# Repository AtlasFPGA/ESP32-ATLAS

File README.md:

# ESP32-ATLAS
   Diseño en desarrollo para el ESP32 DEV KIT V1 usado de forma básica con sus  25 señales,se necesita disponer de un VGA64.
   No podíamos dejar pasar la oportunidad de alojar el ESP32 en el interior de la I/O BOARD ATLAS,este microcontroladro lleva muchos años en el mercado,tant es así que el ESP32 sigue siendo un producto puntero.
   Es importantísimo tener su Software en ATLAS, y con la tercera iteración de correspondencia de pines cubre toda la placa I/O BOARD ATLAS.
   La inicialización de FABGL con su configuración en la mayoría de las placas es la siguiente.
inicialización VGA FABGL:

   Vídeo que muestra, el correcto funcionamiento del recolocador que nos permitirá jugar con audio amplificado, i2s así como i2c en el futuro.

---

## Correcto funcionamiento recolocador ESP32:

---

VGAController.begin(GPIO_NUM_22, GPIO_NUM_21, GPIO_NUM_19, GPIO_NUM_18, GPIO_NUM_5, GPIO_NUM_4, GPIO_NUM_23, GPIO_NUM_15);

Leyendo el quema vemos que significado tiene de señales con sus nombres lógicos de los bits de color así como la frecuencia horizontal y vertical.

VGAController.begin(RED_1, RED_0 , GREEN_1, GREEN_0, BLUE_1, BLUE_0, H_SYNC, V_SYNC)

Inicialización ESP32 en ATLAS con el recolocador creado:

## VGAController.begin(GPIO_NUM_32, GPIO_NUM_33, GPIO_NUM_27, GPIO_NUM_4, GPIO_NUM_17, GPIO_NUM_13, GPIO_NUM_16, GPIO_NUM_15);

El recolocador de ATLAS tiene una colocación diferente.
---

Colocación del ESP32 en la placa I/O Board ATLAS Morada:

---

Placa "La Roja" vista con el recolocador ESP32 desde el bus del sbc:

---

Ensamblado ESP32 visto desde los puertos ps2 y db9 norma atari:

---

Visión de la placa recolocadora ESP32 superior:

---
Visión de la placa recolocadora ESP32 infernior:

---   

# Versión final sin amplificación de sonido:

---   

# Vídeo del proceso de desarrollo del recolocador para ESP32 DEV KIT V1; así como mostrar el funcionamiento del VGA64 222+HS+VS de la placa I/O Board ATLAS:

---

señales ATLAS| aclaración en ESP32 DEV KIT 1 | numero pines
| :--- | ---: | :---:
Señal VGA64 | Casi todos los cores de ESP32 usan 64colores esquema 222+HS+VS | 8
Señal JOYSTICK DB9 | En preparación ATARI-PADDLE-ATLAS  | 6
Señal SD SPI | las señales QPI se usan en modo SPI| 4
Señal PS2 TECLADO  | Protocolo PS/2 | 2
Señal PS2 RATÓN | Protocolo PS/2 | 2
Señal Sonido Estereo | sonido delta sigma_(12bits) o un pwm_(10bits), DAC_ESP32(8bits)| 2
Señal Transmisión y Recepcion | RX TX sin gestión de flujo| 2
Señal EAR | Señal de entrada | 1

   No hay lugar para Las Señales de RX y TX como GPIOS, se tendrá que acceder desde el USB.
   En este diseño son Necesarias 27 señales, pero el ESP32 DEV KIT V1 dispone de 25 patillas/señales de las cuales 4 son de entrada, ahí conectamos las direcciones del mando de juegos de norma ATARI en el bus DB9.

   Inicialmente antes de realizar el recolocador final,hemos usado el esquema de bitluni:
   
   http://www.fabglib.org/conf_v_g_a.html
   
   Con la siguiente disposición de pines para la primera iteración de pines:
   
   VGAController.begin(GPIO_NUM_22, GPIO_NUM_21, GPIO_NUM_19, GPIO_NUM_18, GPIO_NUM_5, GPIO_NUM_4, GPIO_NUM_23, GPIO_NUM_15);

##   Nota importante fijarse en los 4 pines que sólo permiten señales de entrada corresponden a los GPIO36, GPIO39, GPIO34, y GPIO35.

---

# ASIGNACIÓN ACTUAL; buscando tener el I2C con pull up en el DB9 y los 2 DAC de 8bits de resolución en la salida de sonido:
   los GPIO asociados a la salida de los dac de 8bit cada uno son, el GPIO25 y GPIO26.
   Esta es tercera iteración en su configuración final para el recolocador, a nivel lógico, sin amplificación de la señal de audio, para habilitar el puerto de audio con tensiones, es necesario cortar 2 pad stereo para que no llegue la señal a la I/O BOARD ATLAS, y estañar los pads que llevan las señales ESP_AUDIO_8BIT, al conector con tensión 3v3 y GND.

señales ATLAS | Patillaje izquierda | patilaje derecha | señales ATLAS
| ---: | ---: | ---: | :---: 
ENABLE| ENABLE | GPIO23| T14_SD_MOSI
J14_JOY_UP| GPIO36 | GPIO22| K15_JOY_FIRE1
R1_JOY_DOWN| GPIO39 | GPIO01 | MOUSE_DAT
N16_JOY_RIGHT| GPIO34 | GPIO03 | MOUSE_CLK
T15_JOY_LEFT| GPIO35 | GPIO21| K16_JOY_FIRE2
TMDS_2_P| GPIO32 | GPIO19 | R13_SD_MISO
TMDS_2_N| GPIO33 | GPIO18 | T13_SD_CLK
R11_RIGHT| GPIO25 | GPIO05 | R12_SD_CS
T12_LEFT| GPIO26 |GPIO17 | TMDS_O_P
TMDS_1_P| GPIO27 | GPIO16 | TMDSC_N
ATLAS Mini -> L2_KCLK,Morada -> K2_KDAT| GPIO14 | GPIO04 | TMDS_1_N
ATLAS Mini -> K2_KDAT,Morada -> L2_KCLK| GPIO12 | GPIO02 | EAR
TMDS_0_N| GPIO13 | GPIO15 | TMDSC_P
GND| GND | GND| GND
+5V| VIN | +3V3| +3V3

---
# TABLA EQUIVALENCIAS SALIDA CONECTOR DE VÍDEO DIGITAL
Nomenclatura DVI | Pares diferenciales | VGA64 | SCART128 | ZX-SCART
| ---: | ---: | ---: | ---: |:---: 
TMDS[0]|CLK- | HS | CSYNC | CSYNC
TMDS[1]|CLK+ | VS | G[0]  | BRIGHT
TMDS[2]|0-   | BLUE[0] | BLUE[0] | I2S_DIN_SD 
TMDS[3]|0+   | BLUE[1] | BLUE[1] | B
TMDS[4]|1-   | GREEN[0] | G[1] | I2S_BCLK_SCK
TMDS[5]|1+   | GREEN[1] | G[2] | G
TMDS[6]|2-   | RED[0] | RED[0] | I2S_LRC_WS
TMDS[7]|2+   | RED[1] | RED[1] | R

Las señales por determinar del módulo ZX-SCART llevan al menos en serie una resistencia de 270 ohm, pero al ser 3 señales se puede luchar icorporar al DAC de 15 colores un I2S, se han reflejado tanto la terminología de DAC como Micrófono por I2S.

Nota: en modo DVI y anulando los pares diferenciales negativos es decir a 0V, una señal de baja resolución tendría que generar los datos para los 3 colores en digital, y un reloj constate y 5 veces más veloz que el reloj de pixel asociado a su misma resolucion en analógico, en total 4 señales de vídeo digital, no sabemos si estas señales DVI pueden ser generadas.

---

   Esquema de referencia usado al inicio de las iteraciones:

---

   Lo que hace un total de 25 pines GPIO, para aumentar el diseño, esta el DB9 con 6 pines en PULL UP (Consultar esquema ATLAS-MINI), permite ampliarse el modelo existente mediante integrados I2C, con un buses de entrada salida en el bus DB9, tener en cuenta de las otras 4 señales, obligatoriamente tiene que ser señales de entrada.
   
   Consulta del esquema ATLAS MINI "La Roja" con licencia CERN OHL V2 STRICT:
   
   https://github.com/AtlasFPGA/BASECARRIERBOARDATLAS
   
   Consulta del esquema en easyeda:
   
   https://oshwlab.com/subcritical/carrier_io_board_atlas_mini_copy
   
## Dimensiones:

## Las características del Esp32:

Los lenguajes de programación más usados para NodeMCU ESP32, son Arduino y MicroPython. Ambos son de código abierto y cuentan con herramientas de desarrollo gratuitas.
 
## Especificaciones:

• Placa: ESP32 DEVKIT V1 (Espressif)

• SoM (System on module): ESP-WROOM-32 (Espressif)

• SoC (System on chip): ESP32 (ESP32-D0WDQ6)

• Procesador: Tensilica Xtensa Dual-Core 32-bit LX6.

• Frecuencia del reloj: 160 a 240 Mhz.

• Desempeño: Hasta 600 DMIPS

• Memoria:

448 KByte ROM

520 KByte SRAM

16 KByte SRAM in RTC (Real Time Clock)

QSPI Flash/SRAM, 4 MBytes

• Número total de pines GPIO: 25

• WiFi con antena integrada: estándar 802.11 b/g/n. Velocidad de 150.0 Mbps

• Bluetooth: BLE (Bluetooth Low Energy) y Bluetooth Classic

• Interfaz USB-Serial CP2102 on board.

• Modo de funcionamiento Low Power.

• Peripheral Input/Output (25 pines GPIO)

• ADCs (Convertidores Analógico Digital) de 12 bits

• DACs (Convertidores Digital Analógico) de 8 bits

• I²C (Inter-Integrated Circuit)

• UART (Universal Asynchronous Receiver/Transmitter)

• SPI (Serial Peripheral Interface)

• I²S (Integrated Interchip Sound)

• RMII (Reduced Media-Independent Interface)

• PWM (Pulse-Width Modulation).

• Regulador de 3.3 volts on board.

• Voltaje de Alimentación (conector MicroUSB): 5v, 0.5A

• Niveles de voltaje de entradas/salidas: 3.3v

• Corriente máxima en salidas: IOH=40ma (source), IOL=28ma (sink).

- Dimensiones: 51.5 mm x 28.3 mm x 12 mm

- Distancia entre pines: estándar 2.54 mm

- Distancia entre ambas filas de pines: 26.0 mm

- Número total de pines: 30

   Fuente de características y mapeado de pines del microcontrolador de Espressif ESP32.

https://www.puntoflotante.net/NODEMCU-ESP32-DEVKIT-V1-STARTER-KIT.htm

##   En total ATLAS pone a dispocisión con el recolocador ESP32-ATLAS unas 25 señales, completando todas las señales que le puede brindar la I/O BOARD ATLAS: 

Si   hubiera una linea a mayores disponible sería muy interesante que actuara automáticamente un CS_PADDLE sobre el ATARI-PADDLE-ATLAS.

---

---

---

---

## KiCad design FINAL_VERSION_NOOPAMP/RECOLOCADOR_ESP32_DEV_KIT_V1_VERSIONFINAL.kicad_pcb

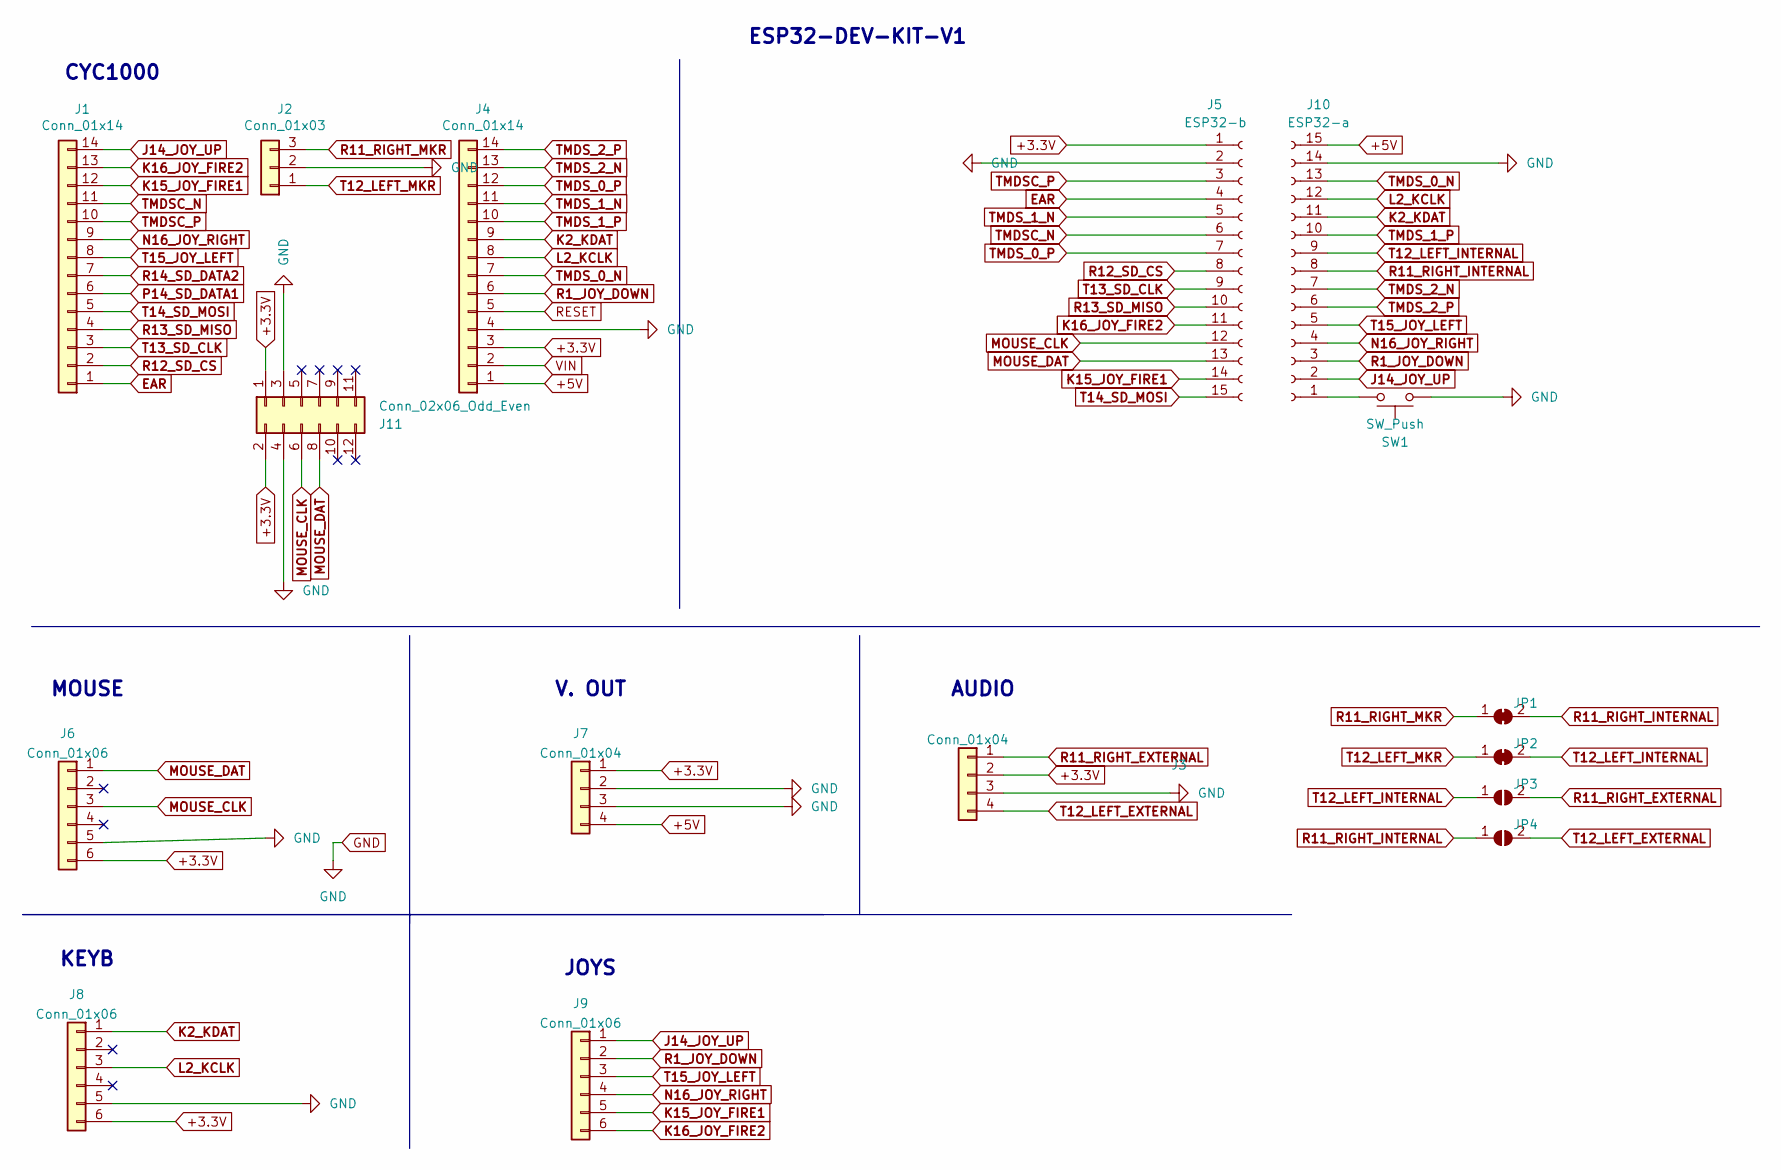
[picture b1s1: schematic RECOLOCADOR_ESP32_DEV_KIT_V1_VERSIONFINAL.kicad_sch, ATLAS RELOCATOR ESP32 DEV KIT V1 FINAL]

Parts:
J1, J4: Conn_01x14; PinHeader_1x14_P2.54mm_Vertical
J2: Conn_01x03; PinHeader_1x03_P2.54mm_Vertical
J3, J7: Conn_01x04; PinHeader_1x04_P2.54mm_Vertical
J5: ESP32-b; PinSocket_1x15_P2.54mm_Vertical
J6, J8, J9: Conn_01x06; PinHeader_1x06_P2.54mm_Vertical
J10: ESP32-a; PinSocket_1x15_P2.54mm_Vertical
J11: Conn_02x06_Odd_Even; PinHeader_2x06_P2.54mm_Vertical
JP1, JP2: SolderJumper_2_Bridged; SolderJumper-2_P1.3mm_Bridged2Bar_RoundedPad1.0x1.5mm
JP3, JP4: SolderJumper_2_Open; SolderJumper-2_P1.3mm_Open_RoundedPad1.0x1.5mm
SW1: SW_Push; SW_PUSH_6mm

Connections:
+3.3V: J3.2, J4.3, J5.1, J6.6, J7.1, J8.6, J11.1, J11.2
+5V: J4.1, J7.4, J10.15
EAR: J1.1, J5.4
GND: J2.2, J3.3, J4.4, J5.2, J6.5, J7.2, J7.3, J8.5, J10.14, J11.3, J11.4, SW1.2
J14_JOY_UP: J1.14, J9.1, J10.2
K2_KDAT: J4.9, J8.1, J10.11
K15_JOY_FIRE1: J1.12, J5.14, J9.5
K16_JOY_FIRE2: J1.13, J5.11, J9.6
L2_KCLK: J4.8, J8.3, J10.12
MOUSE_CLK: J5.12, J6.3, J11.6
MOUSE_DAT: J5.13, J6.1, J11.8
N16_JOY_RIGHT: J1.9, J9.4, J10.4
unnamed: J10.1, SW1.1
P14_SD_DATA1: J1.6
R1_JOY_DOWN: J4.6, J9.2, J10.3
R11_RIGHT_EXTERNAL: J3.1, JP3.2 (B)
R11_RIGHT_INTERNAL: J10.8, JP1.2 (B), JP4.1 (A)
R11_RIGHT_MKR: J2.3, JP1.1 (A)
R12_SD_CS: J1.2, J5.8
R13_SD_MISO: J1.4, J5.10
R14_SD_DATA2: J1.7
RESET: J4.5
T12_LEFT_EXTERNAL: J3.4, JP4.2 (B)
T12_LEFT_INTERNAL: J10.9, JP2.2 (B), JP3.1 (A)
T12_LEFT_MKR: J2.1, JP2.1 (A)
T13_SD_CLK: J1.3, J5.9
T14_SD_MOSI: J1.5, J5.15
T15_JOY_LEFT: J1.8, J9.3, J10.5
TMDSC_N: J1.11, J5.6
TMDSC_P: J1.10, J5.3
TMDS_0_N: J4.7, J10.13
TMDS_0_P: J4.12, J5.7
TMDS_1_N: J4.11, J5.5
TMDS_1_P: J4.10, J10.10
TMDS_2_N: J4.13, J10.7
TMDS_2_P: J4.14, J10.6
VIN: J4.2

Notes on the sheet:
MOUSE
CYC1000
AUDIO
KEYB
JOYS
ESP32-DEV-KIT-V1
V. OUT

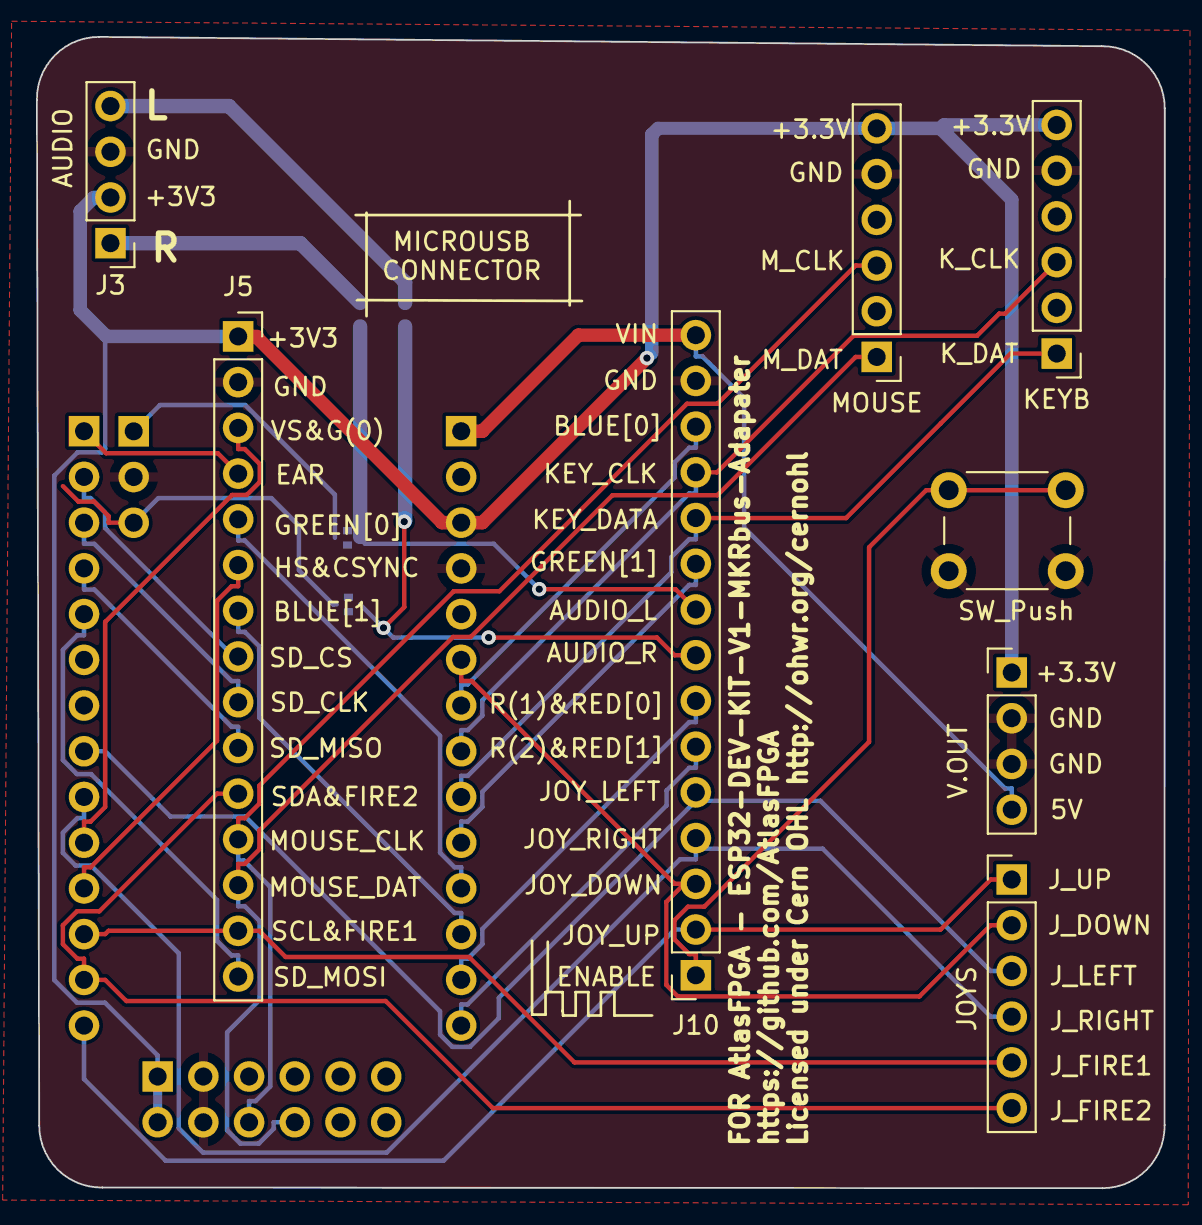
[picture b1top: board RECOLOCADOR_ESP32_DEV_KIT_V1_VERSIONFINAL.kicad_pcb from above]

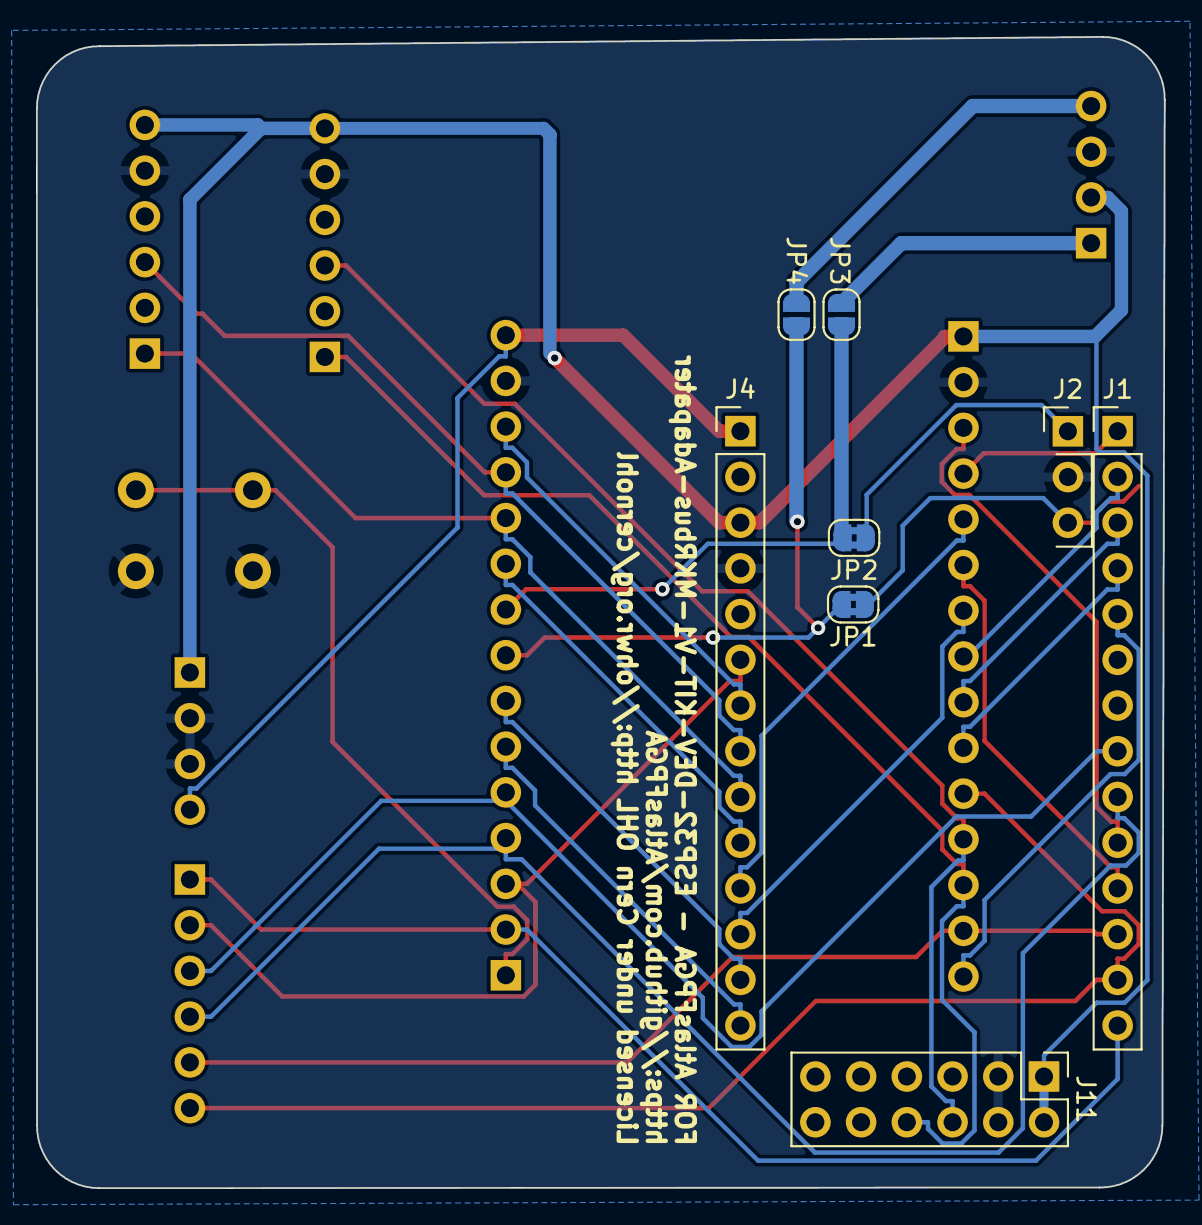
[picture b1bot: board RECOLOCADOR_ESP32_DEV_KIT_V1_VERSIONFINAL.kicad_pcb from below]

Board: 2 copper layers, 62.7 x 64.0 mm, 16 parts (8 on the bottom side), 33 nets.

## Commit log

2023-04-20 Subida de imágenes protipo ESP32-ATLAS.
    Esta vez como hay muchos modelos de ESP32, así como pineados para la VGA222, He optado por una forma clásica de afrontar el problema creando primero un modelo real.
    Se fija el modelo más económico de ESP32 y el más accesibles desde hace casi 8 años, el ESP32 DEV KIT V1.
2023-04-20 Crear un readme con las imágenes iniciales de ESP32-ATLAS
2023-04-20 Especificaciones ESP32
2023-04-20 Pineado ESP32
    Pineado para la versión ESP32 DEV KIT V1, la más usada de todas las versiones de ESP32.
2023-04-20 Añadido Los señales del microcontrolador ESP32 DEV KIT V1
2023-04-20 Agregar características ESP32 DEV KIT V1
2023-04-20 Mejoras en la información relativa al ESP32.
2023-04-20 Información del desarrollo del ESP32-ATLAS
2023-04-20 Añadidas las señales RX y TX sin control de flujo.
2023-04-20 Actualización información ESP32 DEV KIT V1
2023-04-20 Actualizar información ESP32 DEV KIT V1
2023-04-20 Actualización señales I/O BOARD ATLAS, en ESP32.
2023-04-20 Actualizaciones de información sobre el bus multipropósito DB9.
2023-04-20 Añadidas las direcciones de easyeda y kicad de I/O BOARD ATLAS MINI
2023-04-20 Actualización de direcciones easyeda I/O BOARD ATLAS MINI
2023-04-21 Actualización señales en el diseño del ESP32-ATLAS
2023-04-21 Añadidas correspondencias señales ESP32 con I/O Board ATLAS
2023-04-21 Subida paletas y pineado ESP32
2023-04-21 Añadir paletas de colores y pineado del ESP32 DEV KIT V1
2023-04-21 Tabla de correspondencias I/O Board ATLAS y ESP32
2023-04-21 Añadido esquemático de FabGL
2023-04-21 Actualizar correspondencias I/O BOARD ATLAS con ESP32
2023-06-02 Verificación funcionamiento con una placa de prototipo ESP32 en VGA64 con I/O BOARD ATLAS
2023-06-02 ESP32 DEV KIT V1 con la configuración FABGL en I/O BOARD ATLAS
2023-06-04 Nueva asignación final con todos los pines en uso, disponible spi, así como i2c en el puerto DB9.
2023-06-04 Aclaración del modelo kicad de ESP32 KIT V1, copando todos los puertos de la placa I/O Board ATLAS.
2023-06-04 Diseño de recolocador ESP32 DEV KIT V1, usando la misma terminología de recolocador de @Shaeon
2023-06-04 Diseño de recolocador ESP32 DEV KIT V1, usando la misma terminología
2023-06-04 PINEADO ESP32
2023-06-04 Dimensiones ESP32 DEV KIT V1
2023-06-04 Proceso de diseño en desarrollo de un recolocador para el ESP32 DEV KIT V1
2023-06-04 Creación carpeta con placa BETA ESP32 DEV KIT V1
2023-06-04 Diseño BETA considerado final sin amplificador de sonido.
2023-06-04 Versión Beta del recolocador sin amplificación de sonido
2023-06-04 Agregado la versión final sin amplificación de sonido.
2023-06-04 Agregar foto del modelo de recolocador final para placa sin amplificación de sonido
2023-06-04 Update and rename README.md to Agregar información sobre la tabla de correspondencias del VGA64
2023-06-04 Información recolocador ESP32 DEV KIT V1
2023-06-04 Recolocador ESP32 DEV KIT V1 & VGA64
2023-06-04 Actualización del recolocador ESP32 DEV KIT V1 que se muestra en el vídeo.
    Recolocador ESP32 DEV KIT V1:
    https://www.youtube.com/watch?v=cKaD_CqJWqs
2023-06-04 Actualizada información del recolocador para ESP32 DEV KIT V1 VIDEO
2023-06-04 Añadido vídeo diseño.
2023-06-04 Recolocador ESP32 DEV KIT V1
2023-06-04 Añadida información de recolocador ESP32 DEV KIT V1
2023-06-05 Placa RECOLOCADOR ESP32 DEV KIT V1
    Modelo v0011 del recolocador para ESP32 DEV KIT V1, verificada la posición de las señales, el poder disponer de esp32 intercambiables al usar el dev kit v1 permite su reemplazo, la placa escogida es 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
    Hay que tener en cuenta que se han cambiado todas las señales, y no corresponden con FABGL, dado que se busca poder disponer del I2C en el DB9 en las señales de disparo, y cumplir el requisito de 4 s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
    En cuanto a la señal DVI, no sabemos si se podrá conseguir generar una señal DVI de baja resolución, pero el funcionamiento del
2023-06-05 Agregada información del ZX-SCART en desarrollo
2023-06-05 Asignadas las señales para el I2S del ZX-SCART
2023-06-05 Actualizar tabla de correspondencias DAC I2S
2023-06-05 Recolocador SUPERIOR e INFERIOR.
2023-06-05 VERSION FINAL NO_OP_AMP
2023-06-06 Añadir los gerber
2023-06-06 Subida de gerbers último modelo de recolocador para ESP32 DEV KIT V1
2023-06-07 Agregada información en la discrepancia de teclado
    La configuración del ultimo prototipo "LA MORADA" sufrió una inversión de pines en las lienas de datos y reloj asociados al ps2.
    Se ha indicado esta discrepancia en la correspondencia de pines del recolocador.
2023-06-29 Se agregan las fotos de como queda la placa ESP32 para I/O Board ATLAS, en su versión MINI-> La Roja, y el último prototipo "La Morada"
2023-06-29 Subida de las imágenes en el prototipo real para el recolocador ESP32 DEV KIT V1
2023-06-29 Agregar fotografías reales del recolocador ESP32 para todos los modelos de ATLAS.
2023-06-29 Agregada la inicialización de la VGA64 en el recolocador ESP32.
2023-06-29 Modificación datos de la VGA64.
2023-06-29 Agregada la información para la incialización de la vga por parte del ESP32
2023-06-29 Agregada información de la inIcialización de los pines VGA64 del recolocador ESP32 en FABGL
2023-06-29 Inicialización de FABGL con el recolocador ESP32 en IO BOARD ATLAS.
2023-06-30 Agregar vídeo funcionamiento recolocador ESP32
2023-06-30 Agregar Vídeo recolocador ESP32

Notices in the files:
FINAL_VERSION_NOOPAMP/RECOLOCADOR_ESP32_DEV_KIT_V1_VERSIONFINAL.kicad_pcb:
Licensed under Cern OHL http://ohwr.org/cernohl
